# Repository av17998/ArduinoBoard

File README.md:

# AATL Go-Baby-Go Arduino Hat Board

### Designed as a hat board for an Arduino Mega to distribute power and simplify sensor and motor connections. 

## Overall Functions

For this design, the input voltage is 12V, which is split to a linear regulator and to the motor controller for power. The 9V regulator steps down the voltage to input into the Vin pin on the Arduino mega, which will output 5V, which will power the sensors and joysticks. 

There are six pin headers for HCSR04 Ultrasonic Sensors. These sensors are connected in two arrays, one forward and one backwards, designated by "North" and "South". Each array contains three sensors to get a large angle to sense objects in front of or behind the car. The current itteration of the code (uploaded in seperate repo linked below), the sensors are triggered to detect distance depending on which direction the input joystick is moving. 

The joystick is a two axis joystick to be used as the only input method for the vehicle. The only info relevant to this repo is that the joystick takes two 5V and two ground inputs, with one pin each for x and y inputs. 

The motor controller is getting 12V power through a single pole double through EStop switch. When in the normally open position, the motor controller will get 12V power to drive the motors. The motor controller is also connected with the other 6 pin header, which contains enable pins for each motor, and two input pins for each motor. 

## GBR and DRL Files

These files are zipped in zip folders labled by their itteration number. Each of these zip files can be uploaded to a PCB printing website or a GBR file viewer and the PCB designs should be fully portrayed.

## Code Link

https://github.com/av17998/Baby-Car-Code

Design property of Purdue Polytechnic Institute 

## V1.2 Changes

There was an error made in the design that when the EStop switch was in the normally common position, the 12V will be connected straight to ground, so a change has been implemented to connect these pins through a 100k resistor.

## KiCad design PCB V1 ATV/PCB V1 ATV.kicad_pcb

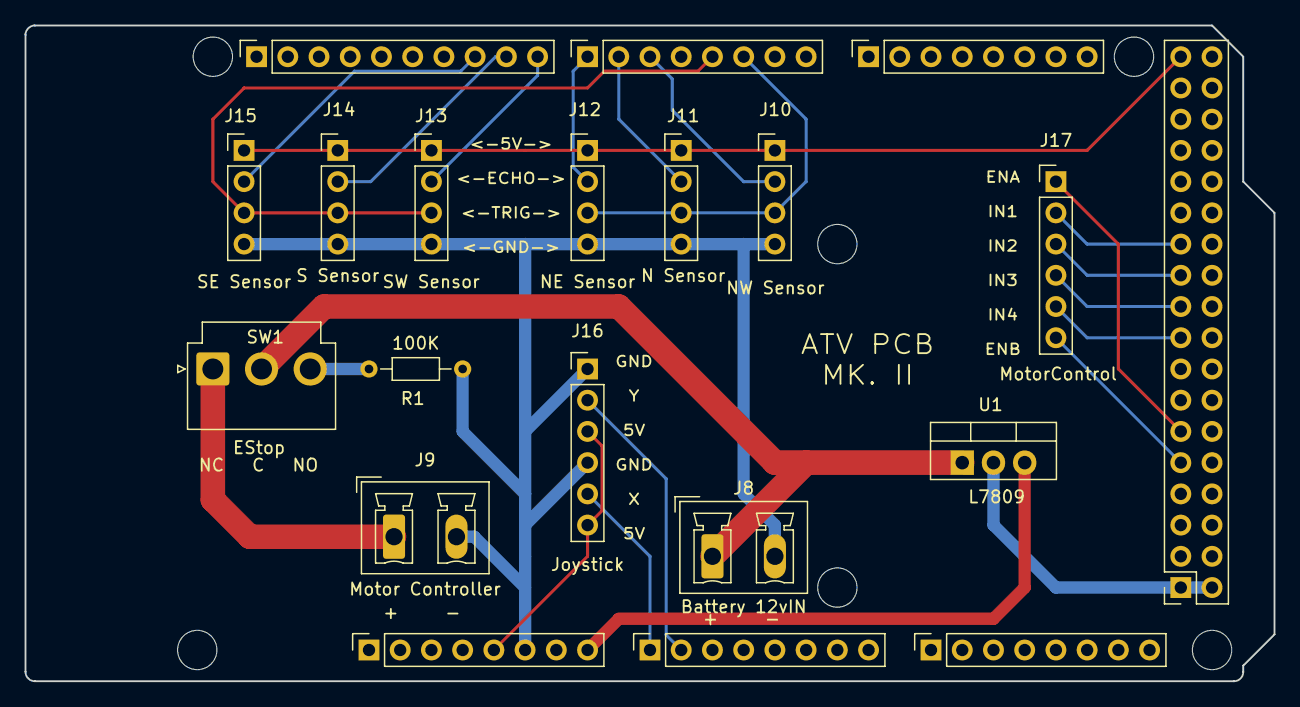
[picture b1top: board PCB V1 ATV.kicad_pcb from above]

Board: 2 copper layers, 101.6 x 53.3 mm, 26 parts (0 on the bottom side), 24 nets.

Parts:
EStop: SW1; JST_VH_B3P-VH-B_1x03_P3.96mm_Vertical
J1: Power; PinSocket_1x08_P2.54mm_Vertical
J2: PWM; PinSocket_1x10_P2.54mm_Vertical
J3, J5: Analog; PinSocket_1x08_P2.54mm_Vertical
J4: PWM; PinSocket_1x08_P2.54mm_Vertical
J6: Communication; PinSocket_1x08_P2.54mm_Vertical
J7: Digital; PinSocket_2x18_P2.54mm_Vertical
J8: Battery 12vIN; Custom 2 Part Phoenix Connector
Joystick: J16; PinHeader_1x06_P2.54mm_Vertical
L7809: U1; TO-220-3_Vertical
MH1, MH2, MH3, MH4, MH5, MH6: MountingHole_3.2mm
Motor Controller : J9; Custom 2 Part Phoenix Connector
MotorControl: J17; PinHeader_1x06_P2.54mm_Vertical
N Sensor: J11; PinHeader_1x04_P2.54mm_Vertical
NE Sensor: J12; PinHeader_1x04_P2.54mm_Vertical
NW Sensor: J10; PinHeader_1x04_P2.54mm_Vertical
R1: 100K; R_Axial_DIN0204_L3.6mm_D1.6mm_P7.62mm_Horizontal
S Sensor: J14; PinHeader_1x04_P2.54mm_Vertical
SE Sensor: J15; PinHeader_1x04_P2.54mm_Vertical
SW Sensor: J13; PinHeader_1x04_P2.54mm_Vertical

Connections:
+5V: J1.5, J7.35, J7.36, Joystick.3, Joystick.6, N Sensor.1, NE Sensor.1, NW Sensor.1, S Sensor.1, SE Sensor.1, SW Sensor.1
/32: J7.23, MotorControl.2
/34: J7.21, MotorControl.3
/36: J7.19, MotorControl.4
/38: J7.17, MotorControl.5
/*2: J4.6, N Sensor.3, NE Sensor.3, NW Sensor.3
/*3: J4.5, S Sensor.3, SE Sensor.3, SW Sensor.3
/*5: J4.3, NW Sensor.2
/*6: J4.2, N Sensor.2
/*7: J4.1, NE Sensor.2
/*8: J2.10, SW Sensor.2
/*9: J2.9, S Sensor.2
/*10: J2.8, SE Sensor.2
/*44: J7.11, MotorControl.1
/*46: J7.9, MotorControl.6
/A0: J3.1, Joystick.5
/A1: J3.2, Joystick.2
/SCL/21: J2.1, J6.8
/SDA/20: J2.2, J6.7
GND: J1.6, J1.7, J2.4, J7.1, J7.2, J8.2, Joystick.1, Joystick.4, L7809.2 (GND), Motor Controller.2, N Sensor.4, NE Sensor.4, NW Sensor.4, R1.2, S Sensor.4, SE Sensor.4, SW Sensor.4
unnamed: EStop.2 (B), J8.1, L7809.1 (IN)
unnamed: EStop.1 (A), Motor Controller.1
unnamed: EStop.3 (C), R1.1
VCC: J1.8, L7809.3 (OUT)

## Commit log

2024-01-09 Initial Commit
    V1 of Board
2024-01-18 V2.0
    Added resistor between estop and ground
2024-01-23 V1.2
    Updated the board to fit the 2 part phoenix connectors, added a resistor, and added more silkscreen. Also removed .gbr and .drl files
2024-01-23 V1.2.1
    Updated the silkscreens
2024-02-01 Adding PCB Image
    Updated backups and PCB Image added
2024-02-01 Update README.md
    Fixed broken image and added code link
